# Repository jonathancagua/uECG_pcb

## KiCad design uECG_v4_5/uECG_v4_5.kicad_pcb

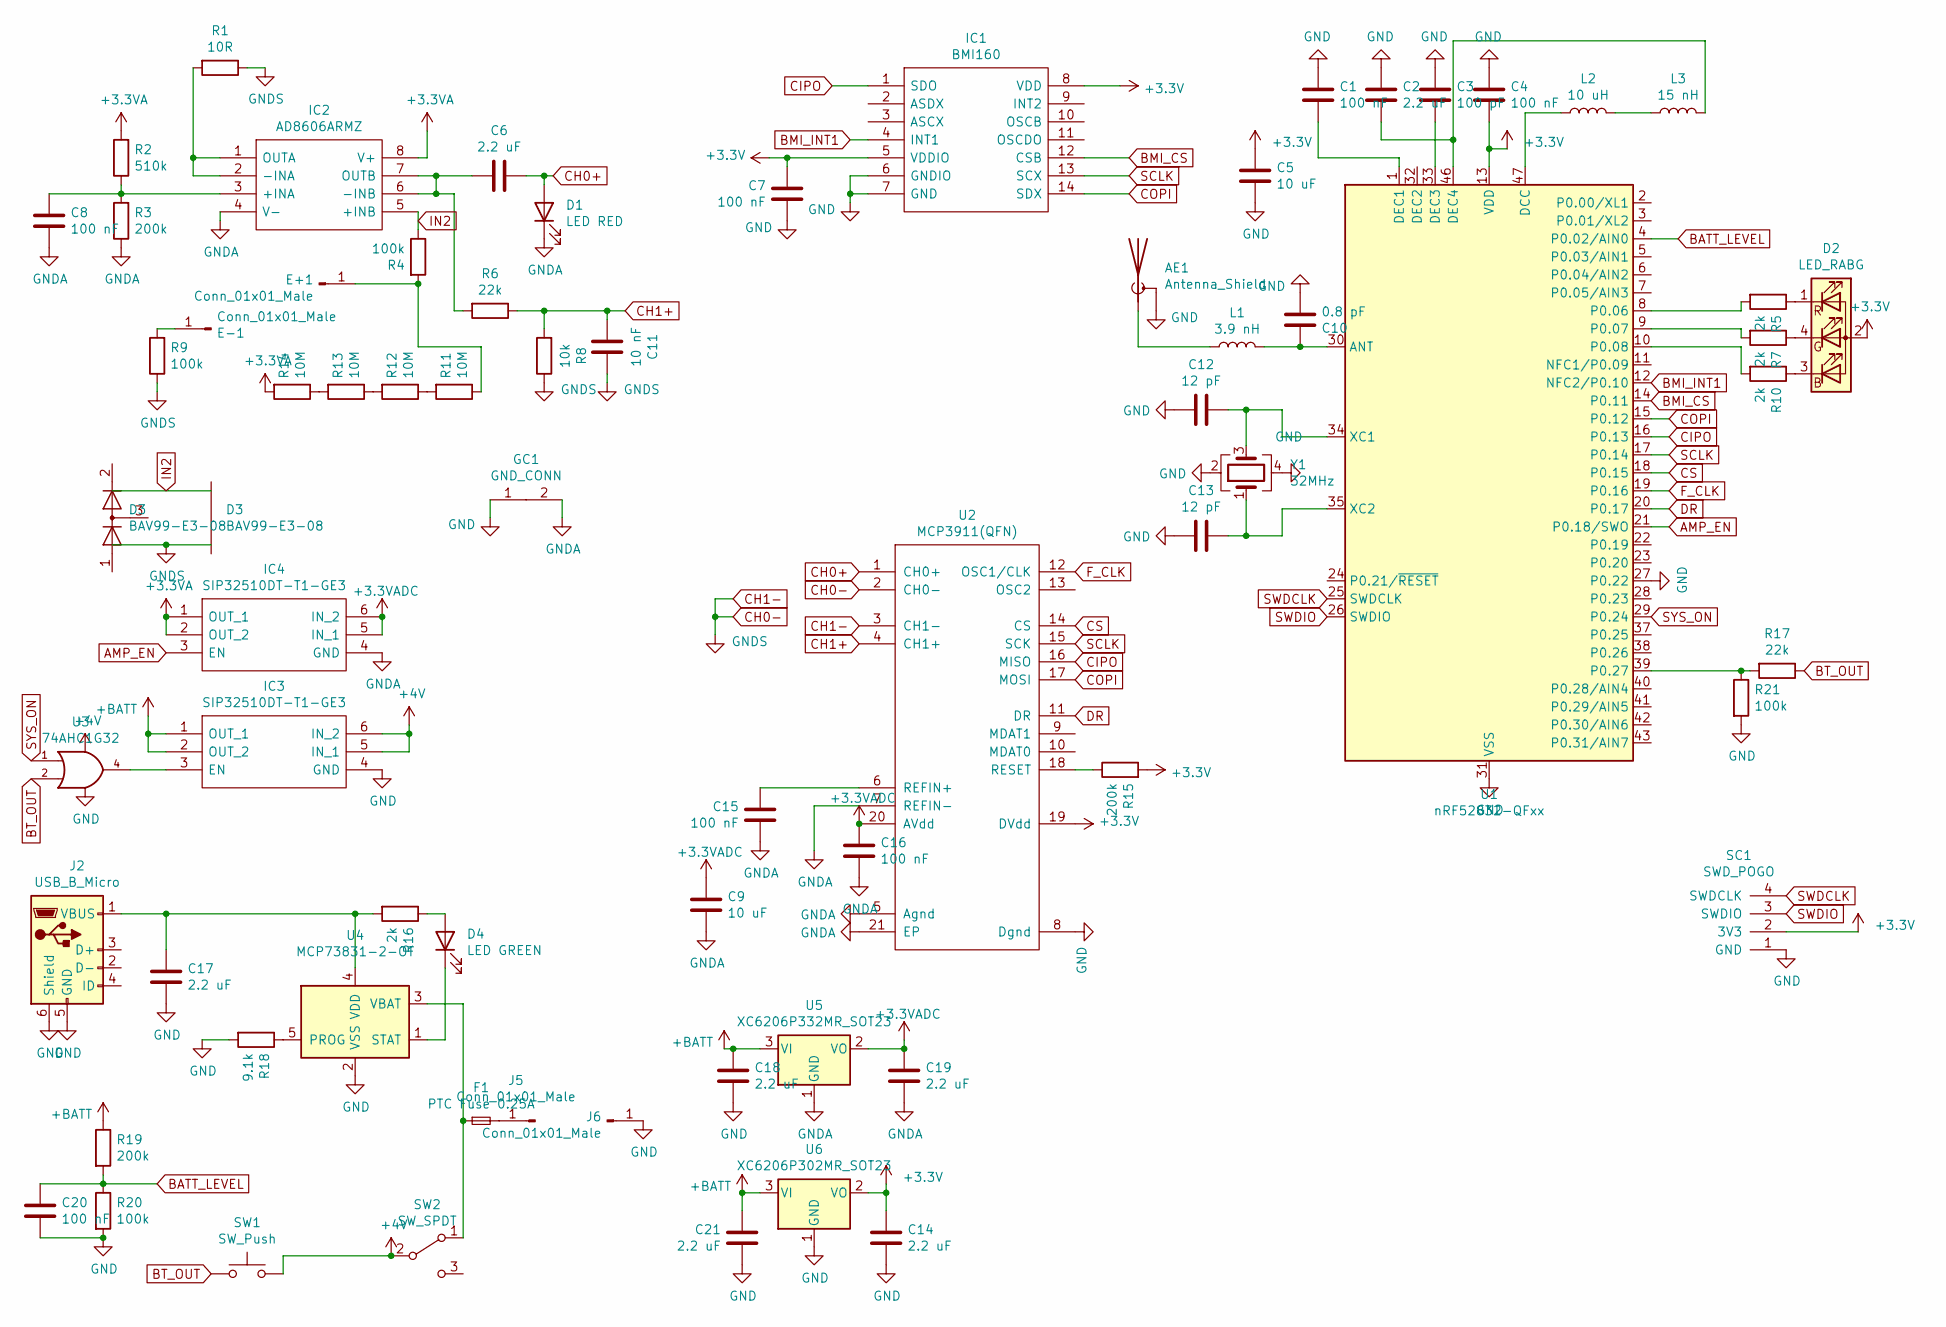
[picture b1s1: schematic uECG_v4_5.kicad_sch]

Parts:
AE1: Antenna_Shield; U.FL_Hirose_U.FL-R-SMT-1_Vertical
C1, C4, C7, C8, C15, C16, C20: 100 nF; C_0402_1005Metric
C2, C6, C14, C17, C18, C19, C21: 2.2 uF; C_0402_1005Metric
C3: 100 pF; C_0402_1005Metric
C5, C9: 10 uF; C_0603_1608Metric
C10: 0.8 pF; C_0402_1005Metric
C11: 10 nF; C_0402_1005Metric
C12, C13: 12 pF; C_0402_1005Metric
D1: LED RED; LED_0603_1608Metric
D2: LED_RABG; LED_RGB_0603
D3: BAV99-E3-08; SOT-23
D4: LED GREEN; LED_0603_1608Metric
E+1: Conn_01x01_Male; PinHeader_1x01_P2.54mm_Vertical
E-1: Conn_01x01_Male; PinHeader_1x01_P2.54mm_Vertical
F1: PTC Fuse 0.25A; Fuse_0603_1608Metric
GC1: GND_CONN
IC1: BMI160; PQFN50P300X250X88-14N; Manufacturer_Part_Number BMI160; Mouser Part Number 262-BMI160
IC2: AD8606ARMZ; MSOP-8_3x3mm_P0.65mm; Manufacturer_Part_Number AD8606ARZ; Mouser Part Number 584-AD8606ARZ
IC3, IC4: SIP32510DT-T1-GE3; TSOT-23-6; Manufacturer_Part_Number SIP32509DT-T1-GE3
J2: USB_B_Micro; conn_usb_B_micro_smd_our
J5: Conn_01x01_Male; Pin_Header_Straight_1x01_Pitch2.54mm
J6: Conn_01x01_Male; PinHeader_1x01_P2.54mm_Vertical
L1: 3.9 nH; L_0402_1005Metric
L2: 10 uH; L_0603_1608Metric
L3: 15 nH; L_0402_1005Metric
R1: 10R; R_0402_1005Metric
R2: 510k; R_0402_1005Metric
R3, R15, R19: 200k; R_0402_1005Metric
R4, R9, R20, R21: 100k; R_0402_1005Metric
R5, R7, R10, R16: 2k; R_0402_1005Metric
R6, R17: 22k; R_0402_1005Metric
R8: 10k; R_0402_1005Metric
R11, R12, R13, R14: 10М; R_0402_1005Metric
R18: 9.1k; R_0402_1005Metric
SC1: SWD_POGO
SW1: SW_Push; BTN_HY_1185
SW2: SW_SPDT; SW_SPDT_PCM12
U1: nRF52832-QFxx; QFN-48-1EP_6x6mm_Pitch0.4mm
U2: MCP3911(QFN); QFN-20-1EP_4x4mm_P0.5mm_EP2.5x2.5mm
U3: 74AHC1G32; SOT-23-5
U4: MCP73831-2-OT; SOT-23-5
U5: XC6206P332MR_SOT23; SOT-23
U6: XC6206P302MR_SOT23; SOT-23
Y1: 32MHz; Crystal_SMD_2016-4Pin_2.0x1.6mm

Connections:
+3.3VA: IC2.8 (V+), IC4.1 (OUT_1), IC4.2 (OUT_2), R2.2, R14.2
+3.3VADC: C9.2, C16.2, C19.2, IC4.5 (IN_1), IC4.6 (IN_2), U2.20 (AVdd), U5.2 (VO)
+3V3: C4.1, C5.2, C7.2, C14.2, D2.2 (A), IC1.5 (VDDIO), IC1.8 (VDD), R15.2, SC1.2 (3V3), U1.13 (VDD), U1.36 (VDD), U1.48 (VDD), U2.19 (DVdd), U6.2 (VO)
+4V: IC3.5 (IN_1), IC3.6 (IN_2), SW1.2, SW2.2 (B), U3.5 (VCC)
+BATT: C18.2, C21.2, IC3.1 (OUT_1), IC3.2 (OUT_2), R19.1, U5.3 (VI), U6.3 (VI)
AMP_EN: IC4.3 (EN), U1.21 (P0.18/SWO)
BATT_LEVEL: C20.2, R19.2, R20.1, U1.4 (P0.02/AIN0)
BMI_CS: IC1.12 (CSB), U1.14 (P0.11)
BMI_INT1: IC1.4 (INT1), U1.12 (NFC2/P0.10)
BT_OUT: R17.1, SW1.1, U3.2
CH0+: C6.2, D1.2 (A), U2.1 (CH0+)
CH0-: C11.2, D3.3 (K), R1.1, R8.1, R9.1, U2.2 (CH0-), U2.3 (CH1-)
CH1+: C11.1, R6.1, R8.2, U2.4 (CH1+)
CIPO: IC1.1 (SDO), U1.16 (P0.13), U2.16 (MISO)
COPI: IC1.14 (SDX), U1.15 (P0.12), U2.17 (MOSI)
CS: U1.18 (P0.15), U2.14 (CS)
DR: U1.20 (P0.17), U2.11 (DR)
F_CLK: U1.19 (P0.16), U2.12 (OSC1/CLK)
GND: AE1.2 (Shield), C1.2, C2.2, C3.2, C4.2, C5.1, C7.1, C10.2, C12.1, C13.1, C14.1, C17.1, C18.1, C20.1, C21.1, GC1.1, IC1.6 (GNDIO), IC1.7 (GND), IC3.4 (GND), J2.5 (GND), J2.6 (Shield), J6.1, R18.2, R20.2, R21.2, SC1.1 (GND), U1.27 (P0.22), U1.31 (VSS), U1.45 (VSS), U1.49 (VSS), U2.8 (Dgnd), U3.3 (GND), U4.2 (VSS), U6.1 (GND), Y1.2, Y1.4
GNDA: C8.1, C9.1, C15.1, C16.1, C19.1, D1.1 (K), GC1.2, IC2.4 (V-), IC4.4 (GND), R3.1, U2.5 (Agnd), U2.7 (REFIN-), U2.21 (EP), U5.1 (GND)
IN2: D3.1 (K), D3.2 (A), IC2.5 (+INB), R4.1
unnamed: AE1.1 (A), L1.1
unnamed: C1.1, U1.1 (DEC1)
unnamed: C2.1, L3.2, U1.46 (DEC4)
unnamed: C3.1, U1.33 (DEC3)
unnamed: C6.1, IC2.6 (-INB), IC2.7 (OUTB), R6.2
unnamed: C8.2, IC2.3 (+INA), R2.1, R3.2
unnamed: C10.1, L1.2, U1.30 (ANT)
unnamed: C12.2, U1.34 (XC1), Y1.3
unnamed: C13.2, U1.35 (XC2), Y1.1
unnamed: C15.2, U2.6 (REFIN+)
unnamed: C17.2, J2.1 (VBUS), R16.2, U4.4 (VDD)
unnamed: D2.1 (RK), R5.1
unnamed: D2.3 (BK), R10.1
unnamed: D2.4 (GK), R7.1
unnamed: D4.1 (K), U4.1 (STAT)
unnamed: D4.2 (A), R16.1
unnamed: E+1.1, R4.2, R11.1
unnamed: E-1.1, R9.2
unnamed: F1.1, SW2.1 (A), U4.3 (VBAT)
unnamed: F1.2, J5.1
unnamed: IC2.1 (OUTA), IC2.2 (-INA), R1.2
unnamed: IC3.3 (EN), U3.4
unnamed: L2.1, U1.47 (DCC)
unnamed: L2.2, L3.1
unnamed: R5.2, U1.8 (P0.06)
unnamed: R7.2, U1.9 (P0.07)
unnamed: R10.2, U1.10 (P0.08)
unnamed: R11.2, R12.1
unnamed: R12.2, R13.1
unnamed: R13.2, R14.1
unnamed: R15.1, U2.18 (RESET)
unnamed: R17.2, R21.1, U1.39 (P0.27)
unnamed: R18.1, U4.5 (PROG)
SCLK: IC1.13 (SCX), U1.17 (P0.14), U2.15 (SCK)
SWDCLK: SC1.4 (SWDCLK), U1.25 (SWDCLK)
SWDIO: SC1.3 (SWDIO), U1.26 (SWDIO)
SYS_ON: U1.29 (P0.24), U3.1

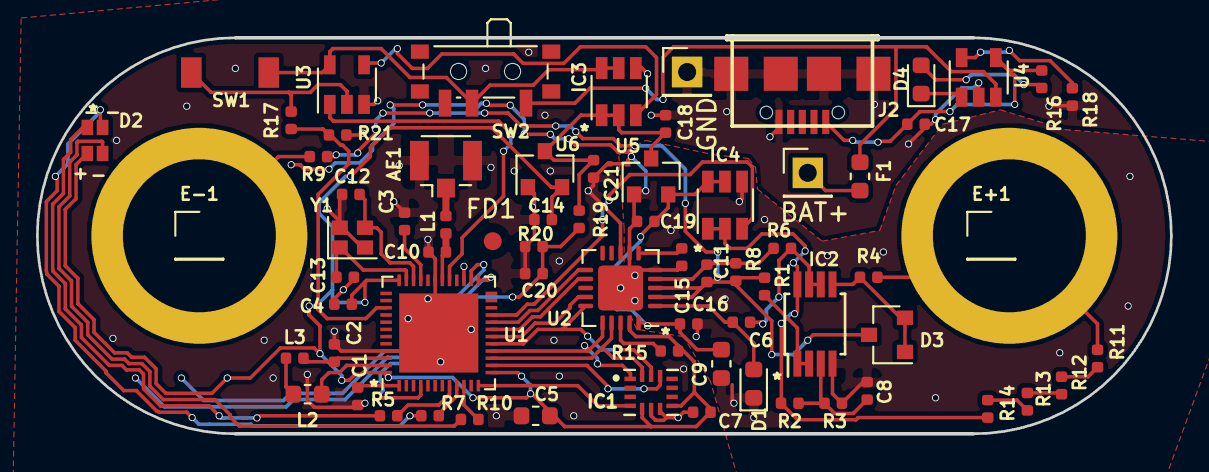
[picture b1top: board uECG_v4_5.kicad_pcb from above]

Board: 2 copper layers, 63.0 x 22.0 mm, 72 parts (1 on the bottom side), 58 nets.

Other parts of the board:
FD1: Fiducial_1mm_Dia_2mm_Outer

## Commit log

2022-04-06 ADD: kicad version 6
